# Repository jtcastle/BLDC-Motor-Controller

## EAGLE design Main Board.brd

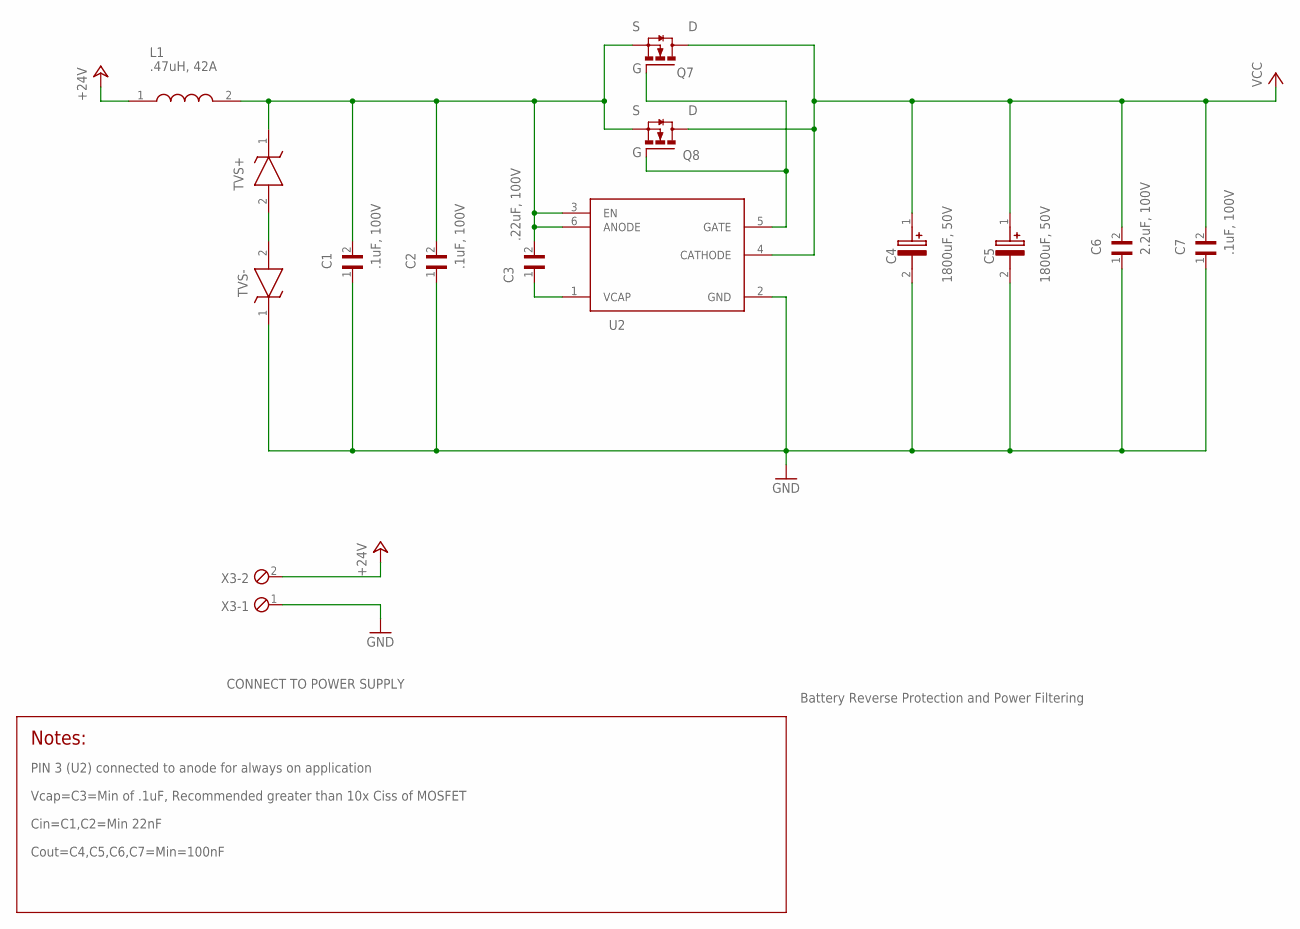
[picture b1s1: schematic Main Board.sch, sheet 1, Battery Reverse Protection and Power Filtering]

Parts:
C1, C2, C7: .1uF, 100V; CAPC2012X145N
C3: .22uF, 100V; CAPC2012X140N
C4, C5: 1800uF, 50V; CAPPRD750W80D1475H4150(HORIZONTAL)
C6: 2.2uF, 100V; CAPC3326X230N
L1: .47uH, 42A; HCM1A1305V2R47R
Q7, Q8: FDBL86361-F085; H-PSOF8L-11.68X9.80_1
TVS+: SMBJ58A-Q; DIOM5436X244N
TVS-: SMBJ26A-Q; DIOM5436X244N
U2: LM74700-Q1MKX-1_NOPB; SOT95P280X145-6N
X3: SCREWTERM_2P_254; 2POL254

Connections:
+24V: L1.1, X3.2
GND: C1.1, C2.1, C4.2 (-), C5.2 (-), C6.1, C7.1, TVS-.1 (K), U2.2 (GND), X3.1; also elsewhere on the board
unnamed: Q7.1 (G), Q8.1 (G), U2.5 (GATE)
unnamed: C3.1, U2.1 (VCAP)
PN$6: C1.2, C2.2, C3.2, L1.2, Q7.2 (S), Q7.3 (S), Q7.4 (S), Q7.5 (S), Q7.6 (S), Q7.7 (S), Q7.8 (S), Q8.2 (S), Q8.3 (S), Q8.4 (S), Q8.5 (S), Q8.6 (S), Q8.7 (S), Q8.8 (S), TVS+.1 (K), U2.3 (EN), U2.6 (ANODE)
PN$25: TVS+.2 (A), TVS-.2 (A)
VCC: C4.1 (+), C5.1 (+), C6.2, C7.2, Q7.9 (D), Q7.10 (D), Q7.11 (D), Q7.12 (D), Q7.13 (D), Q8.9 (D), Q8.10 (D), Q8.11 (D), Q8.12 (D), Q8.13 (D), U2.4 (CATHODE); also elsewhere on the board

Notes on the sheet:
Battery Reverse Protection and Power Filtering
CONNECT TO POWER SUPPLY
PIN 3 (U2) connected to anode for always on application
Vcap=C3=Min of .1uF, Recommended greater than 10x Ciss of MOSFET
Cin=C1,C2=Min 22nF
Cout=C4,C5,C6,C7=Min=100nF

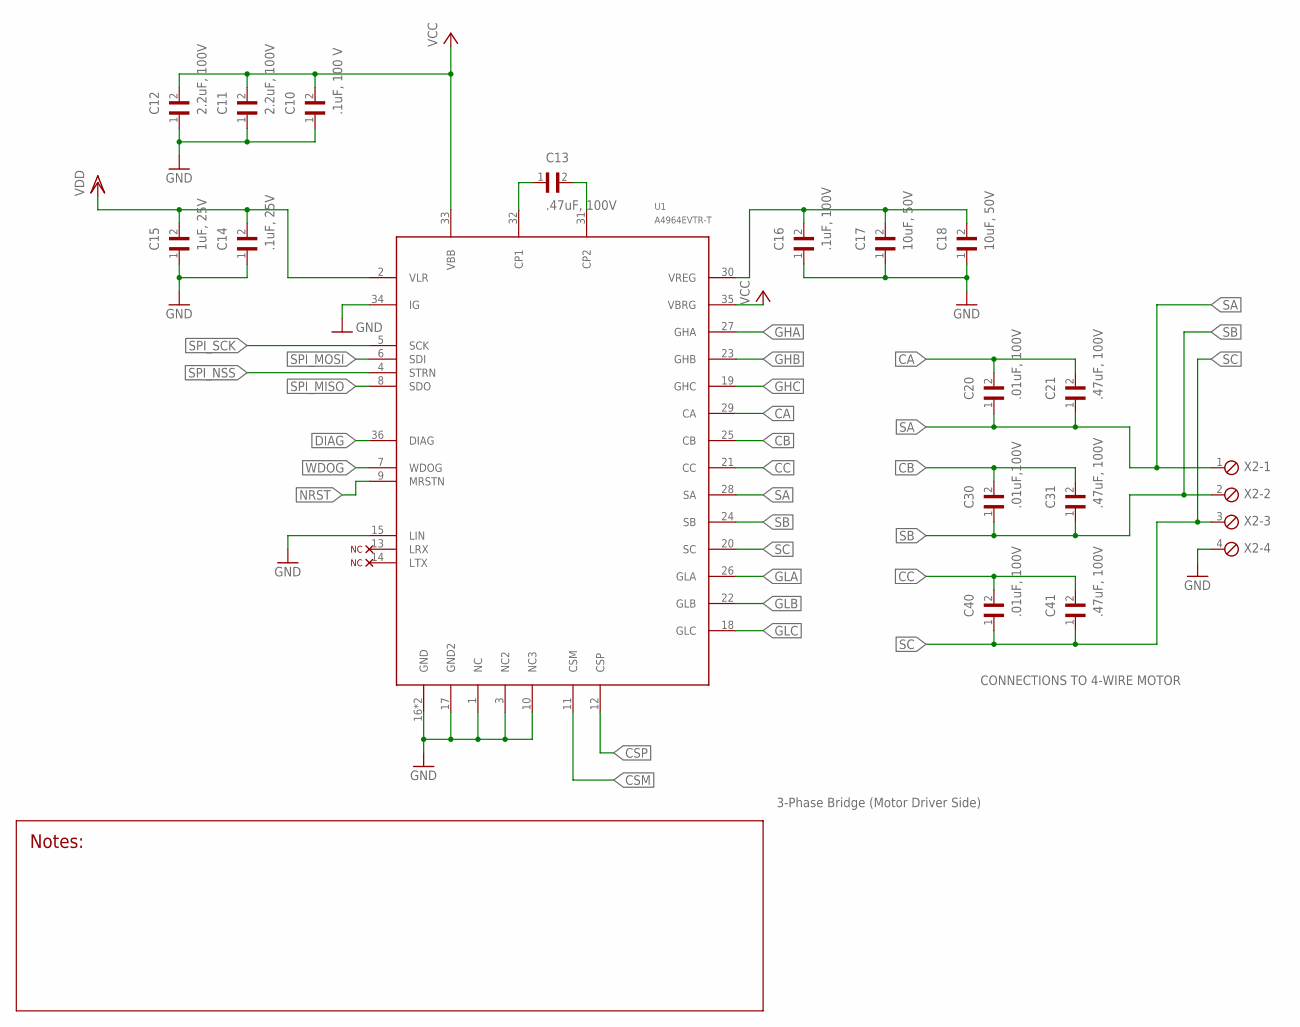
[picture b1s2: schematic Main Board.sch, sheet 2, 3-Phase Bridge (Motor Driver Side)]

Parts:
C10: .1uF, 100 V; CAPC2012X145N
C11, C12: 2.2uF, 100V; CAPC3326X230N
C13, C21, C31, C41: .47uF, 100V; CAPC2012X140N
C14: .1uF, 25V; CAPC1608X90N
C15: 1uF, 25V; CAPC2012X140N
C16: .1uF, 100V; CAPC2012X145N
C17, C18: 10uF, 50V; CAPC3225X280N
C20, C40: .01uF, 100V; CAPC1608X90N
C30: .01uF,100V; CAPC1608X90N
U1: A4964EVTR-T
X2: SCREWTERM_4P_254; 4POL254

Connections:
CA: C20.2, C21.2, U1.29 (CA)
CB: C30.2, C31.2, U1.25 (CB)
CC: C40.2, C41.2, U1.21 (CC)
CSM: U1.11 (CSM); also elsewhere on the board
CSP: U1.12 (CSP); also elsewhere on the board
DIAG: U1.36 (DIAG); also elsewhere on the board
GHA: U1.27 (GHA); also elsewhere on the board
GHB: U1.23 (GHB); also elsewhere on the board
GHC: U1.19 (GHC); also elsewhere on the board
GLA: U1.26 (GLA); also elsewhere on the board
GLB: U1.22 (GLB); also elsewhere on the board
GLC: U1.18 (GLC); also elsewhere on the board
GND: C10.1, C11.1, C12.1, C14.1, C15.1, C16.1, C17.1, C18.1, U1.1 (NC), U1.3 (NC2), U1.10 (NC3), U1.15 (LIN), U1.16 (GND), U1.17 (GND2), U1.34 (IG), U1.37 (GND), X2.4; also elsewhere on the board
unnamed: C13.1, U1.32 (CP1)
unnamed: C13.2, U1.31 (CP2)
NRST: U1.9 (MRSTN); also elsewhere on the board
SA: C20.1, C21.1, U1.28 (SA), X2.1; also elsewhere on the board
SB: C30.1, C31.1, U1.24 (SB), X2.2; also elsewhere on the board
SC: C40.1, C41.1, U1.20 (SC), X2.3; also elsewhere on the board
SPI_MISO: U1.8 (SDO); also elsewhere on the board
SPI_MOSI: U1.6 (SDI); also elsewhere on the board
SPI_NSS: U1.4 (STRN); also elsewhere on the board
SPI_SCK: U1.5 (SCK); also elsewhere on the board
VCC: C10.2, C11.2, C12.2, U1.33 (VBB), U1.35 (VBRG); also elsewhere on the board
VDD: C14.2, C15.2, U1.2 (VLR); also elsewhere on the board
VREG: C16.2, C17.2, C18.2, U1.30 (VREG)
WDOG: U1.7 (WDOG); also elsewhere on the board

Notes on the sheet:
3-Phase Bridge (Motor Driver Side)
CONNECTIONS TO 4-WIRE MOTOR

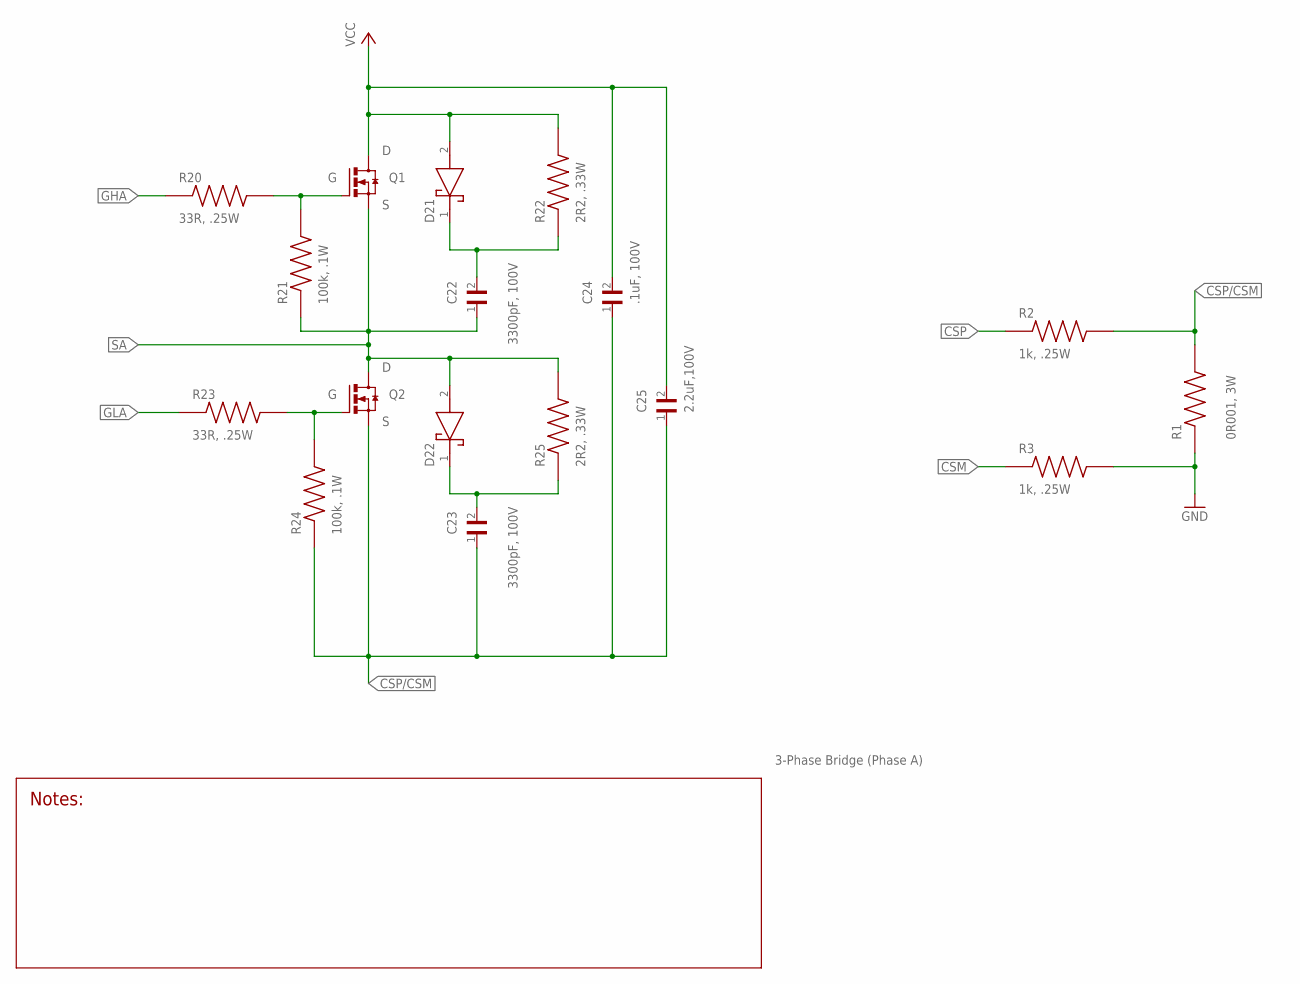
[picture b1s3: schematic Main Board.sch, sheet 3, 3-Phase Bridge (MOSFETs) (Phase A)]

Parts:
C22, C23: 3300pF, 100V; CAPC1608X90N
C24: .1uF, 100V; CAPC2012X145N
C25: 2.2uF,100V; CAPC3326X230N
D21, D22: PMEG6010EP,115; SODFL4725X110N
Q1, Q2: NVMFS5C604NLAFT1G; DFN5_5X6(SO-8FL)_CASE-488AA_IS
R1: 0R001, 3W; RESC6432X90N
R2, R3: 1k, .25W; RESC1608X55N
R20, R23: 33R, .25W; 0805RES
R21, R24: 100k, .1W; RESC1508X50N
R22, R25: 2R2, .33W; RESC1608X55N

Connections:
CSM: R3.1; also elsewhere on the board
CSP: R2.1; also elsewhere on the board
CSP/CSM: C23.1, C24.1, C25.1, Q2.1 (S), Q2.2 (S), Q2.3 (S), R1.2, R2.2, R24.1; also elsewhere on the board
GHA: R20.1; also elsewhere on the board
GLA: R23.1; also elsewhere on the board
GND: R1.1, R3.2; also elsewhere on the board
unnamed: Q1.4 (G), R20.2, R21.2
unnamed: Q2.4 (G), R23.2, R24.2
PN$15: C22.2, D21.1 (K), R22.1
PN$20: C23.2, D22.1 (K), R25.1
SA: C22.1, D22.2 (A), Q1.1 (S), Q1.2 (S), Q1.3 (S), Q2.5 (D), Q2.6 (D), Q2.7 (D), R21.1, R25.2; also elsewhere on the board
VCC: C24.2, C25.2, D21.2 (A), Q1.5 (D), Q1.6 (D), Q1.7 (D), R22.2; also elsewhere on the board

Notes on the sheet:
3-Phase Bridge (Phase A)

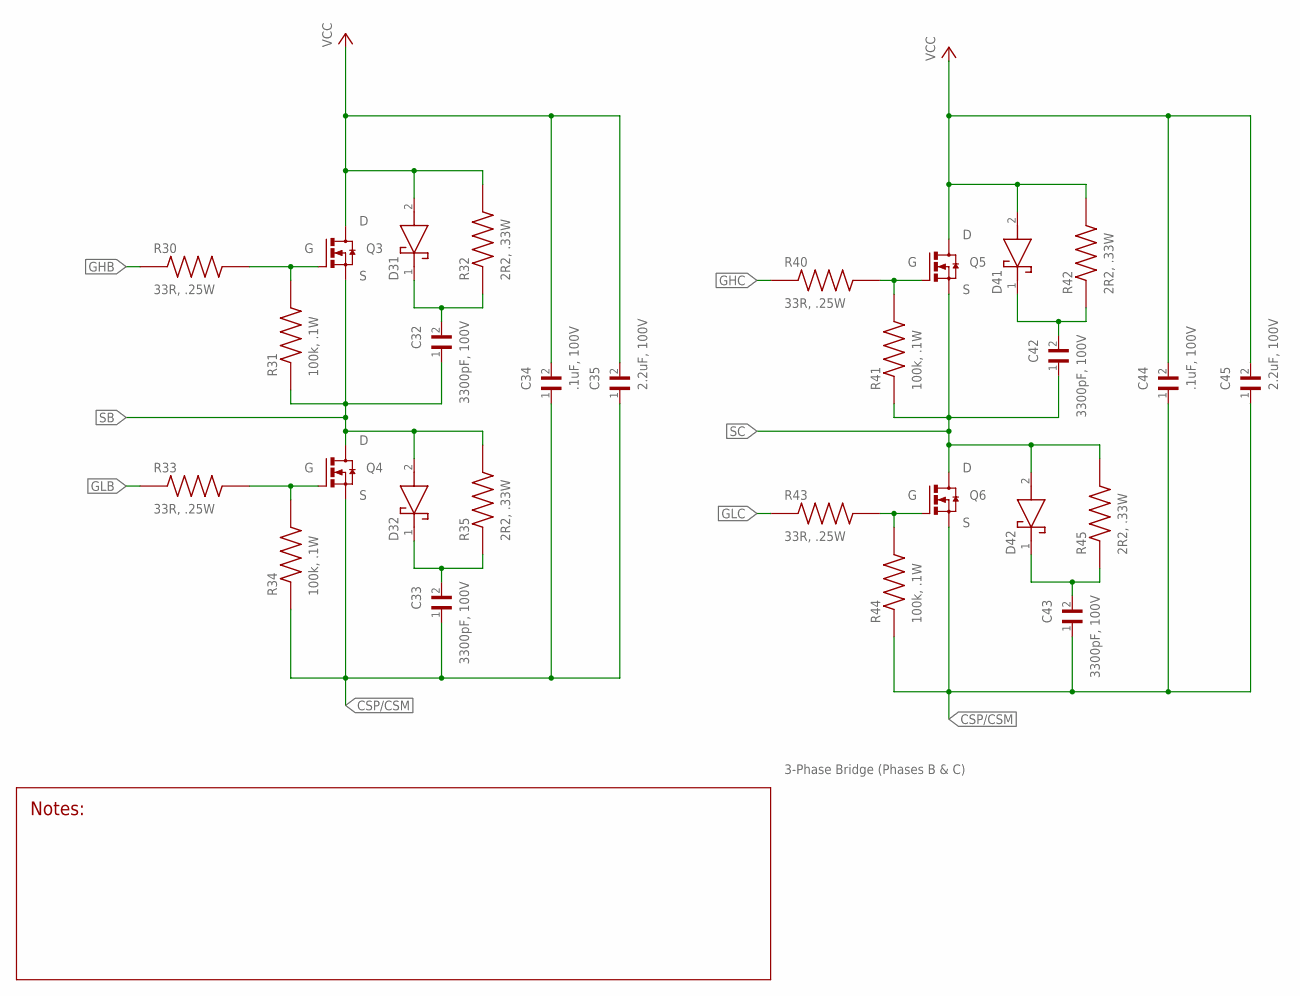
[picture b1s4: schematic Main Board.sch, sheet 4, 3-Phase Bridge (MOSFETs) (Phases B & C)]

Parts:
C32, C33, C42, C43: 3300pF, 100V; CAPC1608X90N
C34, C44: .1uF, 100V; CAPC2012X145N
C35, C45: 2.2uF, 100V; CAPC3326X230N
D31, D32, D41, D42: PMEG6010EP,115; SODFL4725X110N
Q3, Q4, Q5, Q6: NVMFS5C604NLAFT1G; DFN5_5X6(SO-8FL)_CASE-488AA_IS
R30, R33, R40, R43: 33R, .25W; 0805RES
R31, R34, R41, R44: 100k, .1W; RESC1608X55N
R32, R35, R42, R45: 2R2, .33W; RESC1608X55N

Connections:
CSP/CSM: C33.1, C34.1, C35.1, C43.1, C44.1, C45.1, Q4.1 (S), Q4.2 (S), Q4.3 (S), Q6.1 (S), Q6.2 (S), Q6.3 (S), R34.1, R44.1; also elsewhere on the board
GHB: R30.1; also elsewhere on the board
GHC: R40.1; also elsewhere on the board
GLB: R33.1; also elsewhere on the board
GLC: R43.1; also elsewhere on the board
unnamed: Q3.4 (G), R30.2, R31.2
unnamed: Q6.4 (G), R43.2, R44.2
unnamed: Q4.4 (G), R33.2, R34.2
unnamed: Q5.4 (G), R40.2, R41.2
PN$28: C32.2, D31.1 (K), R32.1
PN$29: C33.2, D32.1 (K), R35.1
PN$33: C43.2, D42.1 (K), R45.1
PN$34: C42.2, D41.1 (K), R42.1
SB: C32.1, D32.2 (A), Q3.1 (S), Q3.2 (S), Q3.3 (S), Q4.5 (D), Q4.6 (D), Q4.7 (D), R31.1, R35.2; also elsewhere on the board
SC: C42.1, D42.2 (A), Q5.1 (S), Q5.2 (S), Q5.3 (S), Q6.5 (D), Q6.6 (D), Q6.7 (D), R41.1, R45.2; also elsewhere on the board
VCC: C34.2, C35.2, C44.2, C45.2, D31.2 (A), D41.2 (A), Q3.5 (D), Q3.6 (D), Q3.7 (D), Q5.5 (D), Q5.6 (D), Q5.7 (D), R32.2, R42.2; also elsewhere on the board

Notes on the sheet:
3-Phase Bridge (Phases B & C)

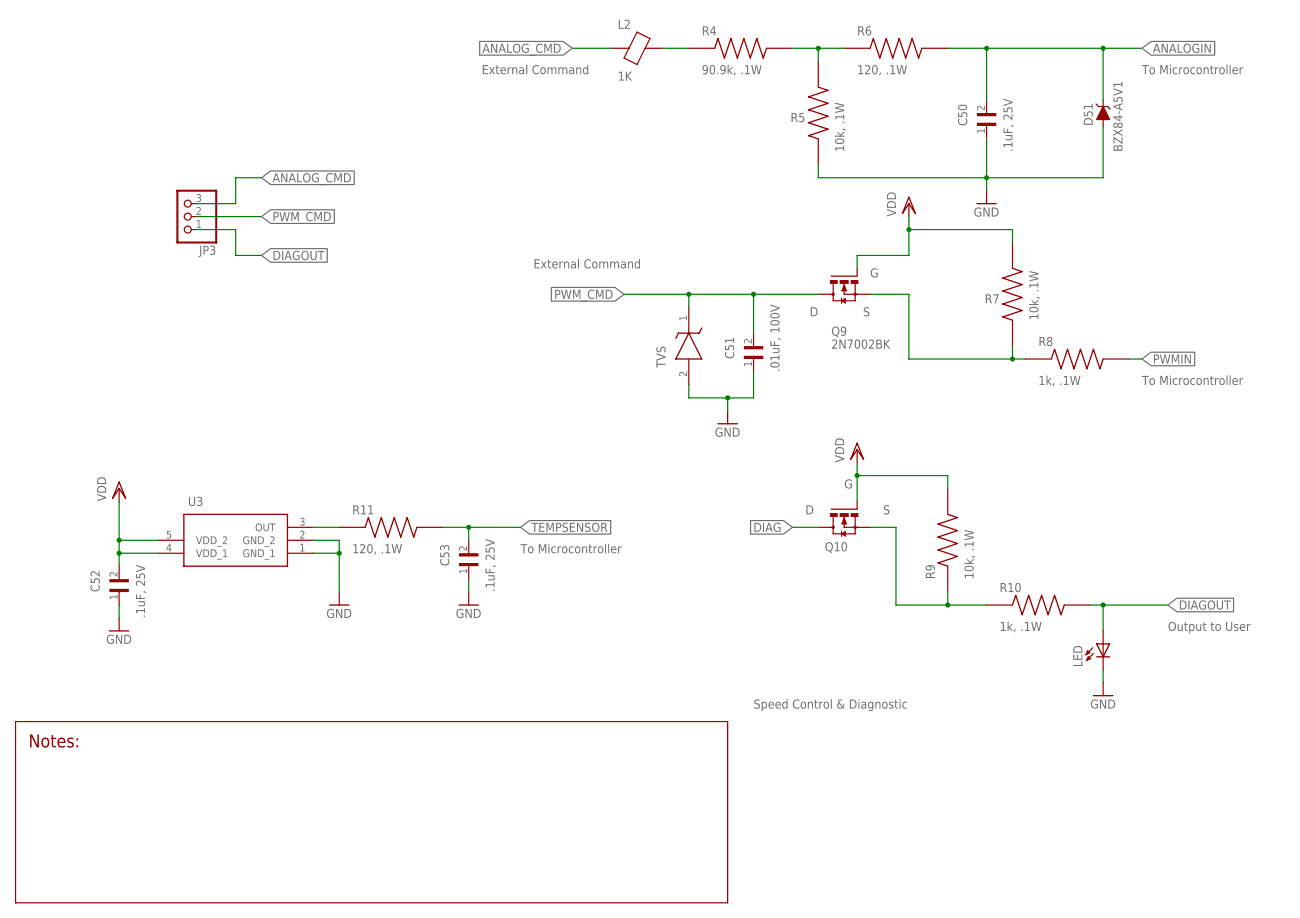
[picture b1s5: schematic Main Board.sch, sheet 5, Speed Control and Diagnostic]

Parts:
C50, C52, C53: .1uF, 25V; CAPC1608X90N
C51: .01uF, 100V; CAPC1608X90N
D51: BZX84-A5V1; SOT95P230X110-3N
JP3: PINHD-1X3; 1X03
L2: 1K; BEADC1608X95N
LED: LTST-C170KRKT; DIOC200X125X110
Q9: 2N7002BK
Q10: BSS123N_H6327
R4: 90.9k, .1W; CAPC1608X90N
R5: 10k, .1W; CAPC1608X90N
R6, R11: 120, .1W; CAPC1608X90N
R7, R9: 10k, .1W; RESC1508X50N
R8, R10: 1k, .1W; RESC1508X50N
TVS: SMBJ30AQ-13-F; DIOM5336X250N
U3: LMT86QDCKRQ1; SOT65P210X110-5N

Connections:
ANALOGIN: C50.2, D51.3 (C), R6.2; also elsewhere on the board
ANALOG_CMD: JP3.3, L2.1
DIAG: Q10.3 (D); also elsewhere on the board
DIAGOUT: JP3.1, LED.+, R10.2
GND: C50.1, C51.1, C52.1, C53.1, D51.1 (A), D51.2 (A), LED.-, R5.1, TVS.2 (A), U3.1 (GND_1), U3.2 (GND_2); also elsewhere on the board
unnamed: R11.1, U3.3 (OUT)
unnamed: R4.2, R5.2, R6.1
unnamed: Q9.2 (S), R7.1, R8.1
unnamed: L2.2, R4.1
unnamed: Q10.2 (S), R9.1, R10.1
PWMIN: R8.2; also elsewhere on the board
PWM_CMD: C51.2, JP3.2, Q9.3 (D), TVS.1 (K)
TEMPSENSOR: C53.2, R11.2; also elsewhere on the board
VDD: C52.2, Q9.1 (G), Q10.1 (G), R7.2, R9.2, U3.4 (VDD_1), U3.5 (VDD_2); also elsewhere on the board

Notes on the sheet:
Speed Control & Diagnostic
External Command
To Microcontroller
Output to User

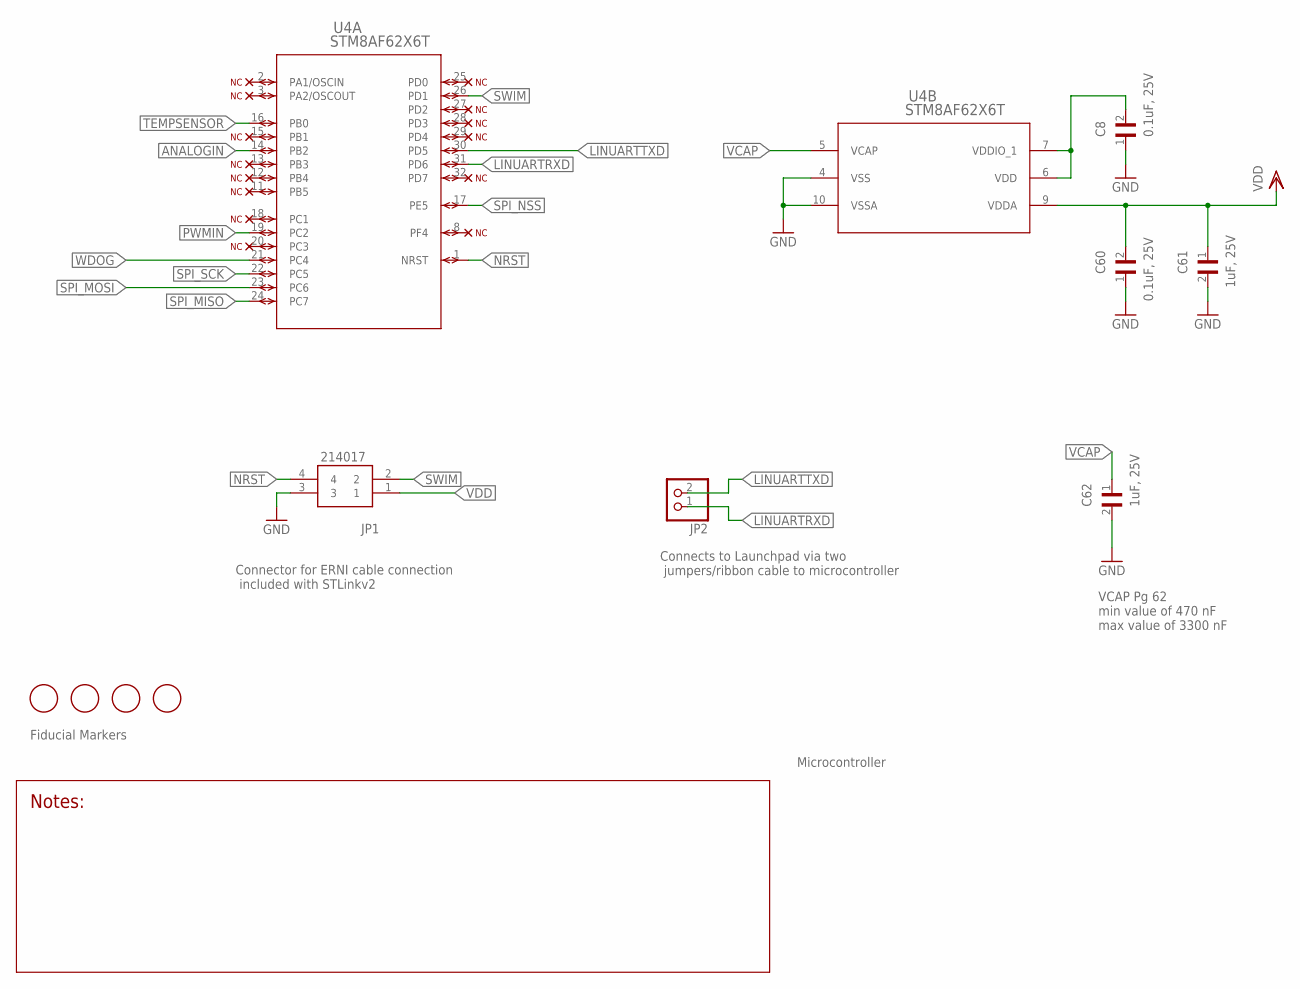
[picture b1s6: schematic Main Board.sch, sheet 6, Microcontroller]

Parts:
C8, C60: 0.1uF, 25V; CAPC1608X90N
C61, C62: 1uF, 25V; CAPC2012X88N
JP1: 214017
JP2: PINHD-1X2; 1X02
U4: STM8AF62X6T; LQFP-32
U$1, U$2, U$3, U$4: FIDUCIAL; FIDUCIAL_1MM

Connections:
ANALOGIN: U4.14 (PB2); also elsewhere on the board
GND: C8.1, C60.1, C61.2, C62.2, JP1.3, U4.4 (VSS), U4.10 (VSSA); also elsewhere on the board
LINUARTRXD: JP2.1, U4.31 (PD6)
LINUARTTXD: JP2.2, U4.30 (PD5)
unnamed: C8.2, U4.6 (VDD), U4.7 (VDDIO_1)
NRST: JP1.4, U4.1 (NRST); also elsewhere on the board
PWMIN: U4.19 (PC2); also elsewhere on the board
SPI_MISO: U4.24 (PC7); also elsewhere on the board
SPI_MOSI: U4.23 (PC6); also elsewhere on the board
SPI_NSS: U4.17 (PE5); also elsewhere on the board
SPI_SCK: U4.22 (PC5); also elsewhere on the board
SWIM: JP1.2, U4.26 (PD1)
TEMPSENSOR: U4.16 (PB0); also elsewhere on the board
VCAP: C62.1, U4.5 (VCAP)
VDD: C60.2, C61.1, JP1.1, U4.9 (VDDA); also elsewhere on the board
WDOG: U4.21 (PC4); also elsewhere on the board

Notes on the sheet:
VCAP Pg 62 min value of 470 nF max value of 3300 nF
Microcontroller
Connects to Launchpad via two jumpers/ribbon cable to microcontroller
Connector for ERNI cable connection included with STLinkv2
Fiducial Markers

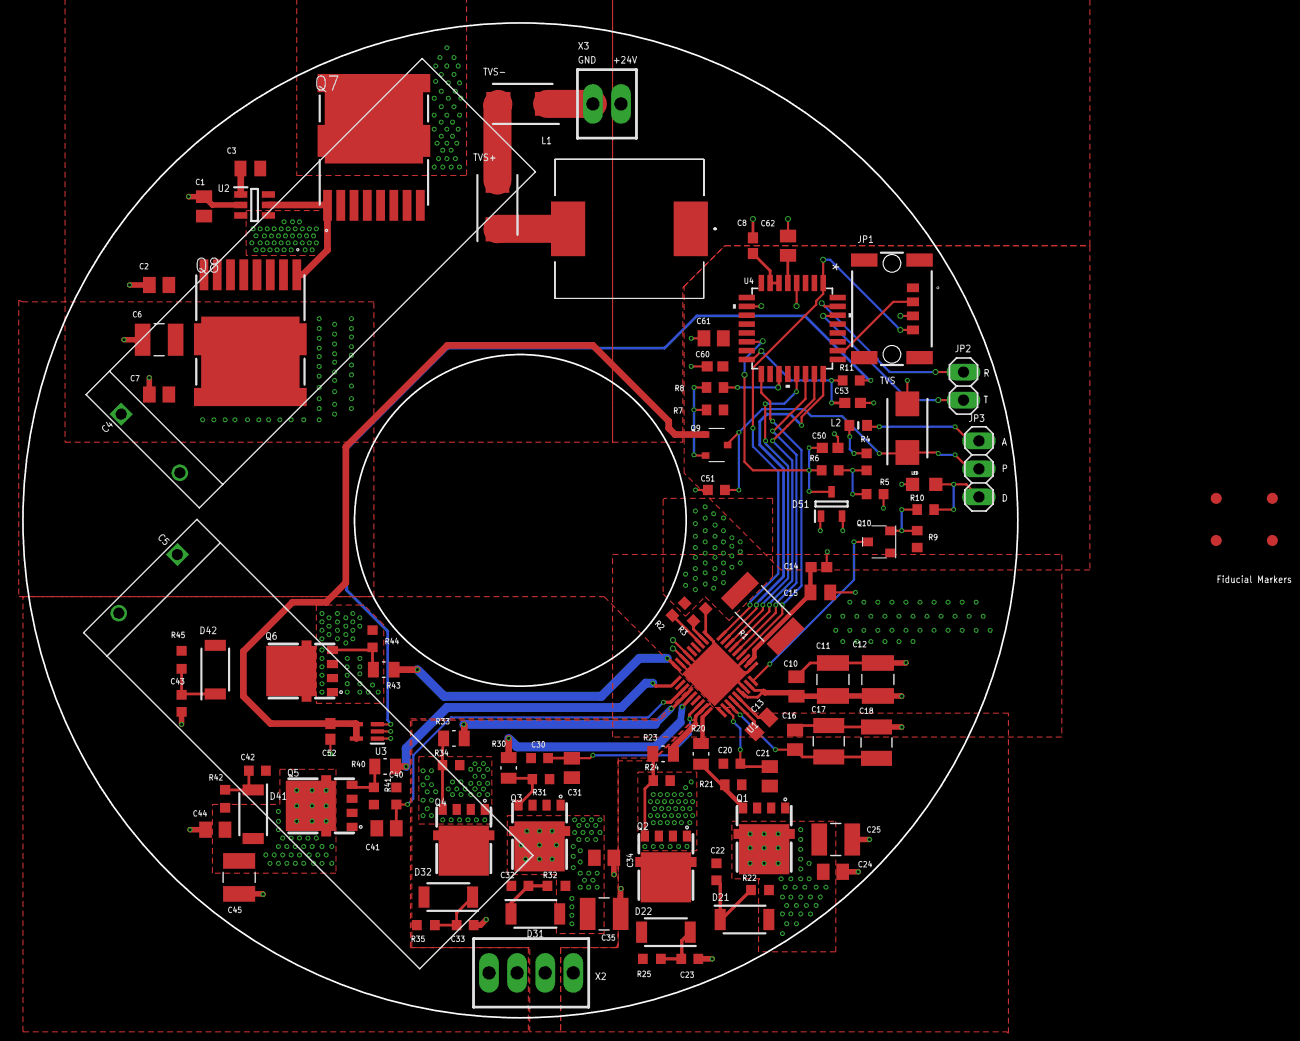
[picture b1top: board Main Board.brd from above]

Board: 4 copper layers, 90.0 x 90.0 mm, 107 parts (0 on the bottom side), 61 nets.

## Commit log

2020-05-12 Uploaded board and corresponding schematic files
2020-05-12 Added Launchpad enclosure files
2020-05-12 Organized 3D Models into folder
2020-05-12 Uploaded Library File
2020-05-22 Files Updated 5-21

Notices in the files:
parts and their libraries:
COPYRIGHT: Copyright (C) 2016 Accelerated Designs. All rights reserved
